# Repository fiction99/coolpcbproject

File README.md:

# coolpcbproject
PCB design and production files for a keypad using the ATMEGA32U4 microcontroller with USB-C integration as well as ESD and overcurrent protection features.

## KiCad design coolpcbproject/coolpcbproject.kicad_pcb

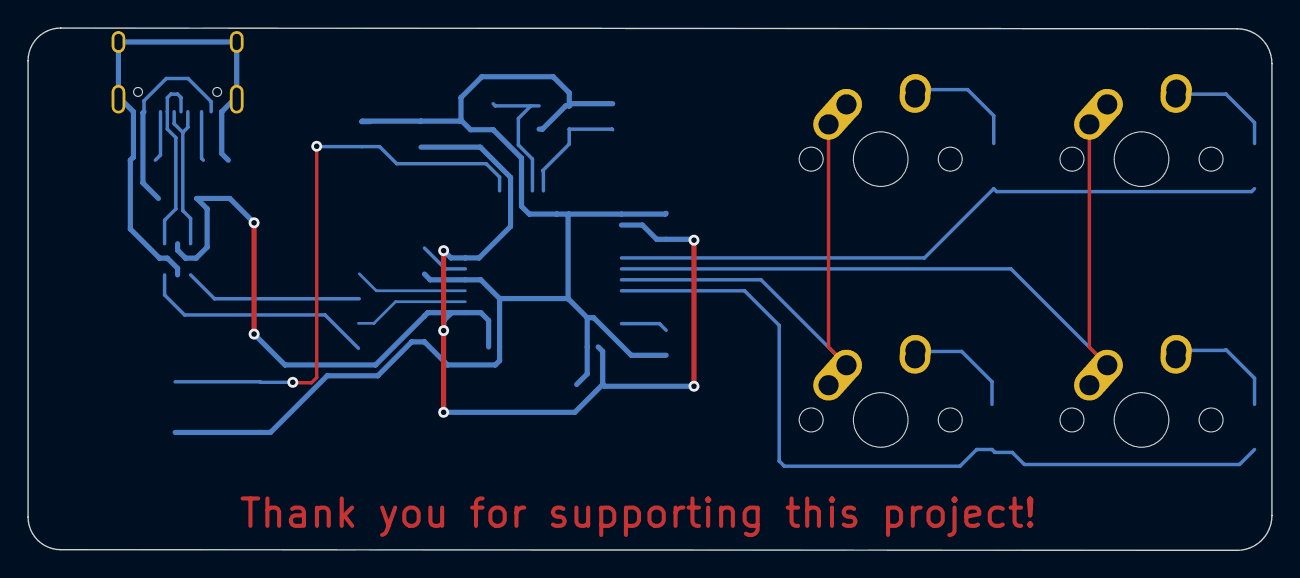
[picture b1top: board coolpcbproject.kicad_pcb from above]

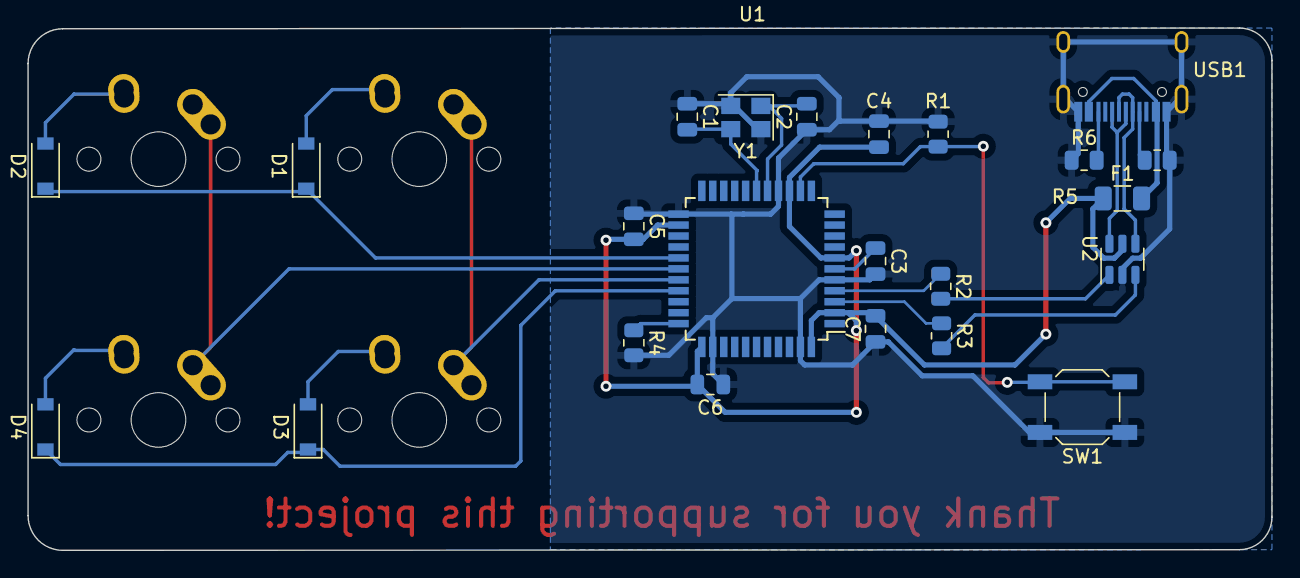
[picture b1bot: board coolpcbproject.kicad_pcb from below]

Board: 2 copper layers, 90.9 x 38.1 mm, 27 parts (23 on the bottom side), 24 nets.

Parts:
C1, C2: 22uF; C_0805_2012Metric
C3: 1uF; C_0805_2012Metric
C4, C5, C6, C7: 0.1uF; C_0805_2012Metric
D1, D2, D3, D4: D_Small; D_SOD-123
F1: 500mA; Fuse_1206_3216Metric
MX1, MX2, MX3, MX4: MX-NoLED; MX-1U-NoLED
R1, R4: 10K; R_0805_2012Metric
R2, R3: 22; R_0805_2012Metric
R5, R6: 5.1K; R_0805_2012Metric
SW1: SW_Push; SW_SPST_SKQG_WithStem
U1: ATmega32U4-A; TQFP-44_10x10mm_P0.8mm
U2: USBLC6-2SC6; SOT-23-6
USB1: HRO-TYPE-C-31-M-12; HRO-TYPE-C-31-M-12-Assembly
Y1: 16 MHz; Crystal_SMD_3225-4Pin_3.2x2.5mm

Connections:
+5V: C4.2, C5.2, C6.2, C7.2, F1.1, U1.2 (UVCC), U1.7 (VBUS), U1.14 (VCC), U1.24 (AVCC), U1.34 (VCC), U1.44 (AVCC), U2.5 (VBUS)
D+: R2.1, U1.4 (D+)
D+ IN: U2.6 (I/O1), USB1.6 (DP1), USB1.8 (DP2)
D+ OUT: R2.2, U2.1 (I/O1)
D-: R3.1, U1.3 (D-)
D- IN: U2.4 (I/O2), USB1.5 (DN2), USB1.7 (DN1)
D- OUT: R3.2, U2.3 (I/O2)
GND: C1.1, C2.1, C3.2, C4.1, C5.1, C6.1, C7.1, R1.2, R4.2, R5.1, R6.1, SW1.1, U1.5 (UGND), U1.15 (GND), U1.23 (GND), U1.35 (GND), U1.43 (GND), U2.2 (GND), USB1.1 (GND), USB1.12 (GND), USB1.13 (SHIELD), Y1.2, Y1.4
unnamed: C1.2, U1.17 (XTAL1), Y1.3
unnamed: C2.2, U1.16 (XTAL2), Y1.1
unnamed: C3.1, U1.6 (UCAP)
unnamed: D1.2 (A), MX1.2 (ROW)
unnamed: D2.2 (A), MX2.2 (ROW)
unnamed: D3.2 (A), MX3.2 (ROW)
unnamed: D4.2 (A), MX4.2 (ROW)
unnamed: R1.1, SW1.2, U1.13 (~RESET)
unnamed: R4.1, U1.33 (~HWB/PE2)
unnamed: R5.2, USB1.4 (CC1)
unnamed: R6.2, USB1.10 (CC2)
Vcc: F1.2, USB1.2 (VBUS), USB1.11 (VBUS)
col0: MX1.1 (COL), MX3.1 (COL), U1.29 (PB5)
col1: MX2.1 (COL), MX4.1 (COL), U1.28 (PB4)
row0: D1.1 (K), D2.1 (K), U1.27 (PD7)
row1: D3.1 (K), D4.1 (K), U1.30 (PB6)

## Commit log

2023-03-04 iteration1
2023-03-04 Add submodules
2023-03-04 adding ai03 library
2023-03-04 re-adding libraries
2023-03-04 removing duplicate library
2023-03-10 adding usb c pretty
2023-03-10 libraries and usb c fix
2023-04-29 finished initial draft
2023-04-29 initial draft 2
    all routing complete, all DRC bugs removed
2023-04-29 gerbers generated
2023-04-29 aesthetic changes
